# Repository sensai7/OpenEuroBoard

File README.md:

# OpenEuroBoard
Kicad and Gerber files for the manufacturing of electronic synthesizers prototyping and developing, focusing on utilities to prototype Eurorack modules. All the sections in the board are independent from each other (except the Gate/CV generators) that need the 5V regulator part, and can be disregarded if they're not needed for the user application.

(This is from an older version but the features are the same)

## Feature List:
 * Size adjusted to fit exactly a standard sized breadboard.
 * SSD1306 driver based Screen interfaces, with sockets for both 128x64px and 128x32px versions.
 * 2x quad op-amps (TL074) for custom use.
 * 5V regulator and power bus.
 * 4x custom push buttons.
 * MIDI IN/OUT interfaces. MIDI IN is isolated through a optocoupler, MIDI OUT is buffered.
 * 8x custom Minijack sockets.
 * 5x pots, 2x custom pots to connect any desired value. The pots can be easily shorted to ground, +12V, or between their own pins using a jumper.
 * 4x custom SPDT switches.
 * 4x custom LEDs.
 * Small jumper storage.
 * A stereo buffered out with a stereo minijack socket.
 * Custom test points and power bus test points.
 * 2x Gate and CV generators, Both signals being 0~5V.
 * 2x oscillators with low (LFO) and high (Audio rate) range switches and frequency pots.
 * Screw mount holes

## Bill Of Materials:
|Section          |Type             |Model                   |Amount|
|-----------------|-----------------|------------------------|------|
|General          |Male Header      |2x5 dupont header       |2     |
|                 |Female Header    |1x40 dupont header      |2     |
|                 |Voltage regulator|LM1117-5                |1     |
|                 |LED              |3mm Red LED             |1     |
|                 |Resistor         |2.2k                    |1     |
|                 |Capacitor        |100n                    |2     |
|                 |Elec. Capacitor  |10u                     |4     |
|Screen interfaces|Screen           |SSD1306                 |1     |
|quad op-amps     |Op. amp          |TL074                   |2     |
|                 |Capacitor        |100n                    |4     |
|Push buttons     |Push button      |6mm push                |4     |
|MIDI IN-OUT      |Din-5 Connector  |Din-5 Connector         |2     |
|                 |Optocoupler      |6n139                   |1     |
|                 |Dual inverter    |CD40107BE               |1     |
|                 |Diode            |1n4148                  |1     |
|                 |Resistor         |220                     |3     |
|                 |Resistor         |270                     |1     |
|                 |Resistor         |120                     |2     |
|Minijack sockets |Minijack         |Thonkiconn jack         |8     |
|Potentiometer    |Potentiometer    |Alps vertical pot       |5     |
|Switches         |SPDT             |8.5mm SPDT              |4     |
|LEDS             |LED              |3mm Red LED             |4     |
|                 |Resistor         |1k                      |4     |
|Jumper storage   |Jumper           |2.54mm jumper           |5     |
|Stereo out       |Op. amp          |TL072                   |1     |
|                 |Capacitor        |100n                    |2     |
|                 |Minijack         |Vertical stereo jack    |1     |
|Gate generators  |Push button      |6mm push                |2     |
|                 |Resistor         |4.7k                    |2     |
|CV Generators    |Potentiometer    |Alps vertical pot 100k  |2     |
|Oscillators      |Op. amp          |Tl074                   |1     |
|                 |Capacitor        |100n                    |4     |
|                 |Potentiometer    |Alps vertical pot 1M LOG|2     |
|                 |SPDT             |8.5mm SPDT              |2     |
|                 |Capacitor        |1u                      |2     |
|                 |Capacitor        |22n                     |2     |
|                 |Resistor         |1k                      |4     |
|                 |Resistor         |10k                     |4     |
|                 |Resistor         |100k                    |2     |

## Changelog

 * V1.0 First version
 * V1.1 Addressed the issues from [Issue 1](https://github.com/sensai7/OpenEuroBoard/issues/1). Updated Silkscreen

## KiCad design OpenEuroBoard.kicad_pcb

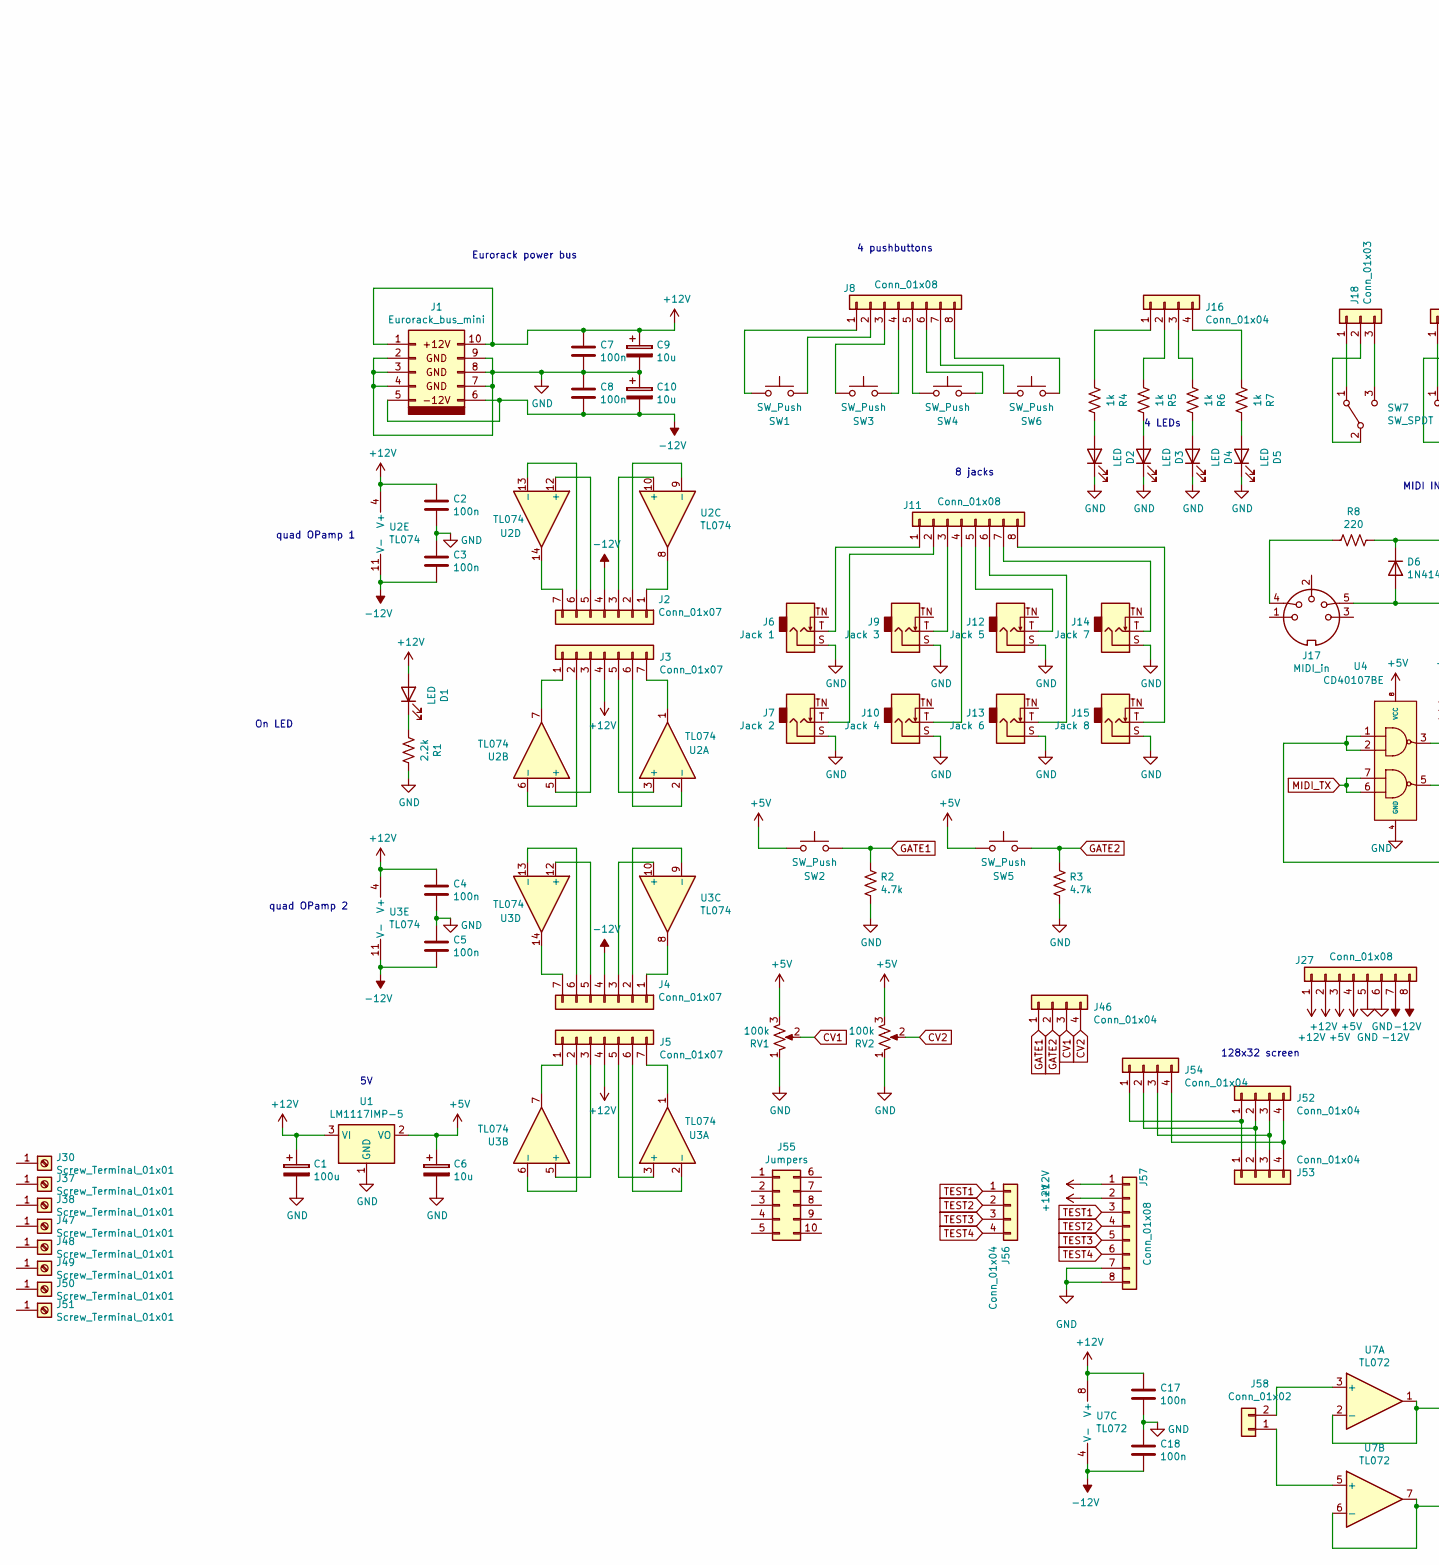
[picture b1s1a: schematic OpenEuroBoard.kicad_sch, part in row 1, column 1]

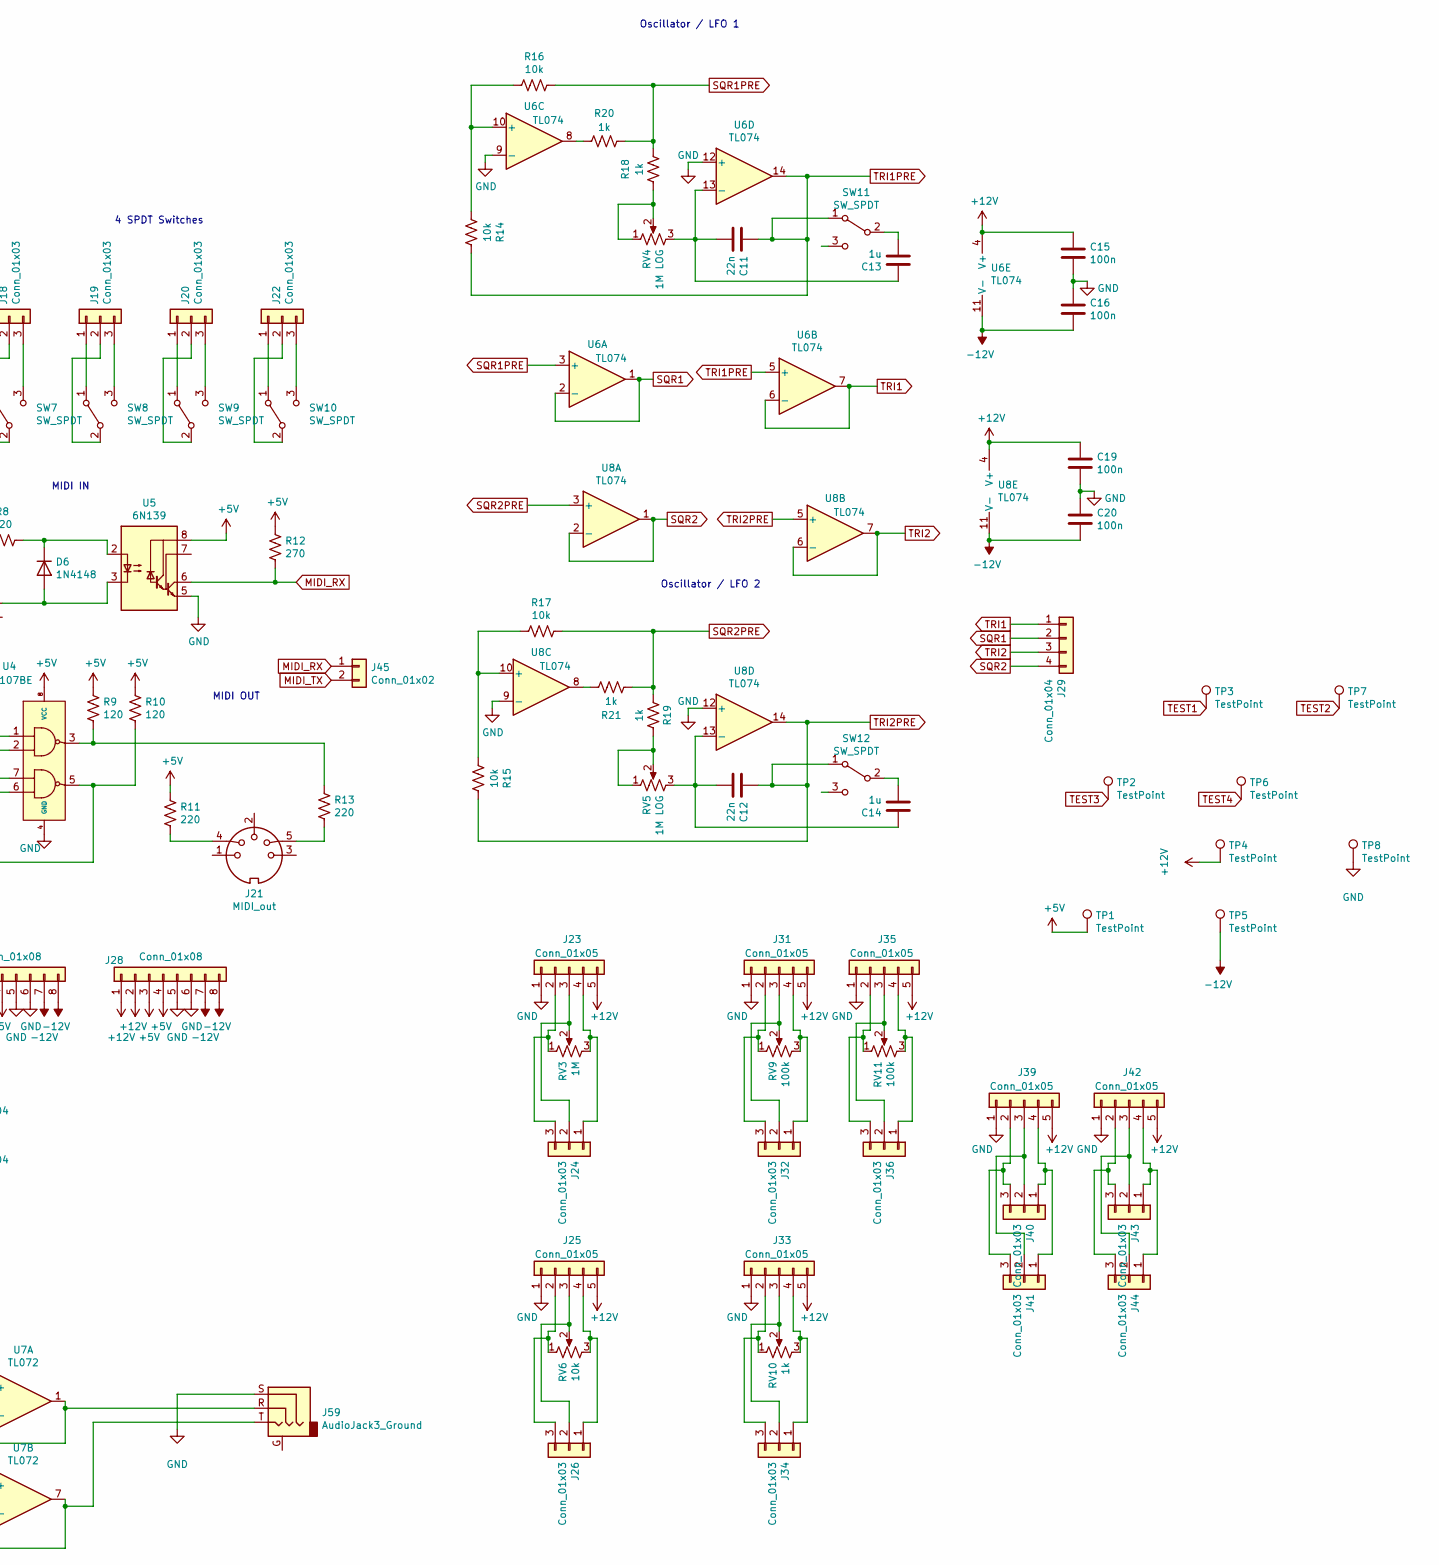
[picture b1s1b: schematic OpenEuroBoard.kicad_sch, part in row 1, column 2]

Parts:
C1: 100u; CP_Radial_D4.0mm_P2.00mm
C2, C3, C4, C5, C7, C8, C15, C16, C17, C18, C19, C20: 100n; C_Disc_D3.4mm_W2.1mm_P2.50mm
C6, C9, C10: 10u; CP_Radial_D4.0mm_P2.00mm
C11, C12: 22n; C_Disc_D3.4mm_W2.1mm_P2.50mm
C13, C14: 1u; C_Disc_D3.4mm_W2.1mm_P2.50mm
D1, D2, D3, D4, D5: LED; LED_D3.0mm_FlatTop
D6: 1N4148; D_DO-35_SOD27_P7.62mm_Horizontal
J1: Eurorack_bus_mini; Eurorack_mini_bus
J2, J3, J4, J5: Conn_01x07; PinHeader_1x07_P2.54mm_Vertical
J6: Jack 1; Jack_3.5mm_QingPu_WQP-PJ398SM_Vertical_CircularHoles
J7: Jack 2; Jack_3.5mm_QingPu_WQP-PJ398SM_Vertical_CircularHoles
J8, J11, J27, J28, J57: Conn_01x08; PinHeader_1x08_P2.54mm_Vertical
J9: Jack 3; Jack_3.5mm_QingPu_WQP-PJ398SM_Vertical_CircularHoles
J10: Jack 4; Jack_3.5mm_QingPu_WQP-PJ398SM_Vertical_CircularHoles
J12: Jack 5; Jack_3.5mm_QingPu_WQP-PJ398SM_Vertical_CircularHoles
J13: Jack 6; Jack_3.5mm_QingPu_WQP-PJ398SM_Vertical_CircularHoles
J14: Jack 7; Jack_3.5mm_QingPu_WQP-PJ398SM_Vertical_CircularHoles
J15: Jack 8; Jack_3.5mm_QingPu_WQP-PJ398SM_Vertical_CircularHoles
J16, J29, J46, J53, J56: Conn_01x04; PinHeader_1x04_P2.54mm_Vertical
J17: MIDI_in; din-5
J18, J19, J20, J22, J24, J26, J32, J34, J36, J40, J41, J43, J44: Conn_01x03; PinHeader_1x03_P2.54mm_Vertical
J21: MIDI_out; din-5
J23, J25, J31, J33, J35, J39, J42: Conn_01x05; PinHeader_1x05_P2.54mm_Vertical
J30, J37, J38, J47, J48, J49, J50, J51: Screw_Terminal_01x01; MountingHole_3.2mm_M3_Pad_Via
J45: Conn_01x02; PinSocket_1x02_P2.54mm_Vertical
J52, J54: Conn_01x04; 0.91 inches 128x32 Screen
J55: Jumpers; PinHeader_2x05_P2.54mm_Vertical
J58: Conn_01x02; PinHeader_1x02_P2.54mm_Vertical
J59: AudioJack3_Ground; Jack Stereo vertical Thonk
R1: 2.2k; R_Axial_DIN0207_L6.3mm_D2.5mm_P7.62mm_Horizontal
R2, R3: 4.7k; R_Axial_DIN0207_L6.3mm_D2.5mm_P7.62mm_Horizontal
R4, R5, R6, R7, R18, R19, R20, R21: 1k; R_Axial_DIN0207_L6.3mm_D2.5mm_P7.62mm_Horizontal
R8, R11, R13: 220; R_Axial_DIN0207_L6.3mm_D2.5mm_P7.62mm_Horizontal
R9, R10: 120; R_Axial_DIN0207_L6.3mm_D2.5mm_P7.62mm_Horizontal
R12: 270; R_Axial_DIN0207_L6.3mm_D2.5mm_P7.62mm_Horizontal
R14, R15, R16, R17: 10k; R_Axial_DIN0207_L6.3mm_D2.5mm_P7.62mm_Horizontal
RV1, RV2, RV9, RV11: 100k; trimmer_alps-rk09k1130ah1
RV3: 1M; trimmer_alps-rk09k1130ah1
RV4, RV5: 1M LOG; trimmer_alps-rk09k1130ah1
RV6: 10k; trimmer_alps-rk09k1130ah1
RV10: 1k; trimmer_alps-rk09k1130ah1
SW1, SW2, SW3, SW4, SW5, SW6: SW_Push; SW_PUSH_6mm_H5mm
SW7, SW8, SW9, SW10, SW11, SW12: SW_SPDT; SPDT_8.5x3.7mm_SS12d00G4
TP1, TP2, TP3, TP4, TP5, TP6, TP7, TP8: TestPoint; TestPoint_THTPad_D3.0mm_Drill1.5mm
U1: LM1117IMP-5; TO-220-3_Horizontal_TabDown
U2, U3: TL074
U4: CD40107BE; DIP-8_W7.62mm_LongPads
U5: 6N139; DIP-8_W7.62mm
U6, U8: TL074; DIP-14_W7.62mm
U7: TL072; DIP-8_W7.62mm_Socket_LongPads

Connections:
+5V: C6.1, J27.3, J27.4, J28.3, J28.4, R9.1, R10.1, R11.1, R12.1, RV1.3, RV2.3, SW2.1, SW5.1, TP1.1, U1.2 (VO), U4.8 (VCC), U5.8 (VCC)
+12V: C1.1, C2.1, C4.1, C7.1, C9.1, C15.1, C17.1, C19.1, D1.2 (A), J1.1, J1.10, J3.4, J5.4, J23.5, J25.5, J27.1, J27.2, J28.1, J28.2, J31.5, J33.5, J35.5, J39.5, J42.5, J57.1, J57.2, TP4.1, U1.3 (VI), U2.4 (V+), U3.4 (V+), U6.4 (V+), U7.8 (V+), U8.4 (V+)
-12V: C3.2, C5.2, C8.2, C10.2, C16.2, C18.2, C20.2, J1.5, J1.6, J2.4, J4.4, J27.7, J27.8, J28.7, J28.8, TP5.1, U2.11 (V-), U3.11 (V-), U6.11 (V-), U7.4 (V-), U8.11 (V-)
CV1: J46.3, RV1.2
CV2: J46.4, RV2.2
GATE1: J46.1, R2.1, SW2.2
GATE2: J46.2, R3.1, SW5.2
GND: C1.2, C2.2, C3.1, C4.2, C5.1, C6.2, C7.2, C8.1, C9.2, C10.1, C15.2, C16.1, C17.2, C18.1, C19.2, C20.1, D2.1 (K), D3.1 (K), D4.1 (K), D5.1 (K), J1.2, J1.3, J1.4, J1.7, J1.8, J1.9, J6.S, J7.S, J9.S, J10.S, J12.S, J13.S, J14.S, J15.S, J23.1, J25.1, J27.5, J27.6, J28.5, J28.6, J31.1, J33.1, J35.1, J39.1, J42.1, J57.7, J57.8, J59.S, R1.1, R2.2, R3.2, RV1.1, RV2.1, TP8.1, U1.1 (GND), U4.4 (GND), U5.5 (GND), U6.9 (-), U6.12 (+), U8.9 (-), U8.12 (+)
MIDI_RX: J45.1, R12.2, U5.6 (VO2)
MIDI_TX: J45.2, U4.6, U4.7
unnamed: D1.1 (K), R1.2
unnamed: D2.2 (A), R4.1
unnamed: D3.2 (A), R5.1
unnamed: D4.2 (A), R6.1
unnamed: D5.2 (A), R7.1
unnamed: D6.2 (A), J17.5, U5.3 (C2)
unnamed: D6.1 (K), R8.1, U5.2 (C1)
unnamed: J2.1, U2.8
unnamed: J2.2, U2.9 (-)
unnamed: J2.3, U2.10 (+)
unnamed: J2.5, U2.12 (+)
unnamed: J2.6, U2.13 (-)
unnamed: J2.7, U2.14
unnamed: J3.1, U2.7
unnamed: J3.2, U2.6 (-)
unnamed: J3.3, U2.5 (+)
unnamed: J3.5, U2.3 (+)
unnamed: J3.6, U2.2 (-)
unnamed: J3.7, U2.1
unnamed: J4.1, U3.8
unnamed: J4.2, U3.9 (-)
unnamed: J4.3, U3.10 (+)
unnamed: J4.5, U3.12 (+)
unnamed: J4.6, U3.13 (-)
unnamed: J4.7, U3.14
unnamed: J5.1, U3.7
unnamed: J5.2, U3.6 (-)
unnamed: J5.3, U3.5 (+)
unnamed: J5.5, U3.3 (+)
unnamed: J5.6, U3.2 (-)
unnamed: J5.7, U3.1
unnamed: J8.1, SW1.1
unnamed: J8.2, SW1.2
unnamed: J8.3, SW3.1
unnamed: J8.4, SW3.2
unnamed: J8.5, SW4.1
unnamed: J8.6, SW4.2
unnamed: J8.7, SW6.1
unnamed: J8.8, SW6.2
unnamed: J6.T, J11.1
unnamed: J7.T, J11.2
unnamed: J9.T, J11.3
unnamed: J10.T, J11.4
unnamed: J11.5, J12.T
unnamed: J11.6, J13.T
unnamed: J11.7, J14.T
unnamed: J11.8, J15.T
unnamed: J16.1, R4.2
unnamed: J16.2, R5.2
unnamed: J16.3, R6.2
unnamed: J16.4, R7.2
unnamed: J17.4, R8.2
unnamed: J18.1, SW7.1 (A)
unnamed: J18.2, SW7.2 (B)
unnamed: J18.3, SW7.3 (C)
unnamed: J19.1, SW8.1 (A)
unnamed: J19.2, SW8.2 (B)
unnamed: J19.3, SW8.3 (C)
unnamed: J20.1, SW9.1 (A)
unnamed: J20.2, SW9.2 (B)
unnamed: J20.3, SW9.3 (C)
unnamed: J21.4, R11.2
unnamed: J21.5, R13.2
unnamed: J22.1, SW10.1 (A)
unnamed: J22.2, SW10.2 (B)
unnamed: J22.3, SW10.3 (C)
unnamed: J23.2, J24.3, RV3.1
unnamed: J23.3, J24.2, RV3.2
unnamed: J23.4, J24.1, RV3.3
unnamed: J25.2, J26.3, RV6.1
unnamed: J25.3, J26.2, RV6.2
unnamed: J25.4, J26.1, RV6.3
unnamed: J31.2, J32.3, RV9.1
unnamed: J31.3, J32.2, RV9.2
unnamed: J31.4, J32.1, RV9.3
unnamed: J33.2, J34.3, RV10.1
unnamed: J33.3, J34.2, RV10.2
unnamed: J33.4, J34.1, RV10.3
unnamed: J35.2, J36.3, RV11.1
unnamed: J35.3, J36.2, RV11.2
unnamed: J35.4, J36.1, RV11.3
unnamed: J39.2, J40.3, J41.3
unnamed: J39.3, J40.2, J41.2
unnamed: J39.4, J40.1, J41.1
unnamed: J42.2, J43.3, J44.3
unnamed: J42.3, J43.2, J44.2
unnamed: J42.4, J43.1, J44.1
unnamed: J52.1, J53.1, J54.1
unnamed: J52.2, J53.2, J54.2
unnamed: J52.3, J53.3, J54.3
unnamed: J52.4, J53.4, J54.4
unnamed: J58.1, U7.5 (+)
unnamed: J58.2, U7.3 (+)
unnamed: R10.2, U4.1, U4.2, U4.5
unnamed: R9.2, R13.1, U4.3
unnamed: R18.1, RV4.1, RV4.2
unnamed: R19.1, RV5.1, RV5.2
unnamed: R20.1, U6.8
unnamed: R21.2, U8.8
unnamed: C13.2, SW11.2 (B)
unnamed: C14.2, SW12.2 (B)
unnamed: R14.2, R16.2, U6.10 (+)
unnamed: C11.2, C13.1, RV4.3, U6.13 (-)
unnamed: J59.R, U7.1, U7.2 (-)
unnamed: J59.T, U7.6 (-), U7.7
unnamed: R15.2, R17.2, U8.10 (+)
unnamed: C12.2, C14.1, RV5.3, U8.13 (-)
SQR1: J29.2, U6.1, U6.2 (-)
SQR1PRE: R16.1, R18.2, R20.2, U6.3 (+)
SQR2: J29.4, U8.1, U8.2 (-)
SQR2PRE: R17.1, R19.2, R21.1, U8.3 (+)
TEST1: J56.1, J57.3, TP3.1
TEST2: J56.2, J57.4, TP7.1
TEST3: J56.3, J57.5, TP2.1
TEST4: J56.4, J57.6, TP6.1
TRI1: J29.1, U6.6 (-), U6.7
TRI1PRE: C11.1, R14.1, SW11.1 (A), U6.5 (+), U6.14
TRI2: J29.3, U8.6 (-), U8.7
TRI2PRE: C12.1, R15.1, SW12.1 (A), U8.5 (+), U8.14

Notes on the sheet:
4 pushbuttons
MIDI OUT
8 jacks
quad OPamp 1
4 SPDT Switches
128x32 screen
Eurorack power bus
quad OPamp 2
Oscillator / LFO 2
MIDI IN
4 LEDs
Oscillator / LFO 1
On LED

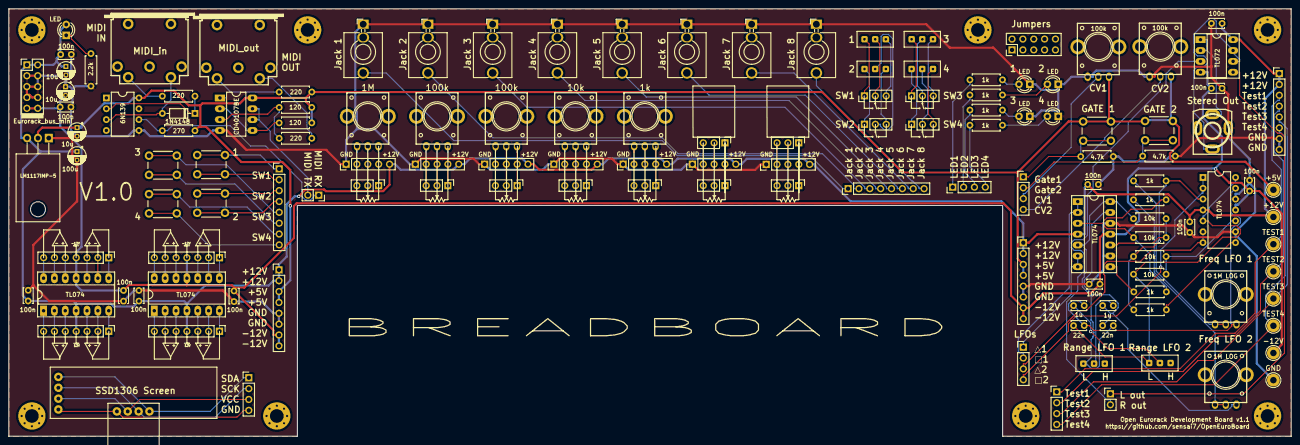
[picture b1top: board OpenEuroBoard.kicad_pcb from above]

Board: 2 copper layers, 300.0 x 100.0 mm, 143 parts (0 on the bottom side), 129 nets.

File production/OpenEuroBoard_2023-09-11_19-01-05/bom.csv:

Designator,Footprint,Quantity,Value,LCSC Part #
C1,CP_Radial_D4.0mm_P2.00mm,1,100u,
"C10, C6, C9",CP_Radial_D4.0mm_P2.00mm,3,10u,
"C11, C12",C_Disc_D3.4mm_W2.1mm_P2.50mm,2,22n,
"C13, C14",C_Disc_D3.4mm_W2.1mm_P2.50mm,2,1u,
"C15, C16, C17, C18, C19, C2, C20, C3, C4, C5, C7, C8",C_Disc_D3.4mm_W2.1mm_P2.50mm,12,100n,
"D1, D2, D3, D4, D5",LED_D3.0mm_FlatTop,5,LED,
D6,D_DO-35_SOD27_P7.62mm_Horizontal,1,1N4148,
J1,Eurorack_mini_bus,1,Eurorack_bus_mini,
J10,Jack_3.5mm_QingPu_WQP-PJ398SM_Vertical_CircularHoles,1,Jack 4,
"J11, J27, J28, J57, J8",PinHeader_1x08_P2.54mm_Vertical,5,Conn_01x08,
J12,Jack_3.5mm_QingPu_WQP-PJ398SM_Vertical_CircularHoles,1,Jack 5,
J13,Jack_3.5mm_QingPu_WQP-PJ398SM_Vertical_CircularHoles,1,Jack 6,
J14,Jack_3.5mm_QingPu_WQP-PJ398SM_Vertical_CircularHoles,1,Jack 7,
J15,Jack_3.5mm_QingPu_WQP-PJ398SM_Vertical_CircularHoles,1,Jack 8,
"J16, J29, J46, J53, J56",PinHeader_1x04_P2.54mm_Vertical,5,Conn_01x04,
J17,din-5,1,MIDI_in,
"J18, J19, J20, J22, J24, J26, J32, J34, J36, J40, J41, J43, J44",PinHeader_1x03_P2.54mm_Vertical,13,Conn_01x03,
"J2, J3, J4, J5",PinHeader_1x07_P2.54mm_Vertical,4,Conn_01x07,
J21,din-5,1,MIDI_out,
"J23, J25, J31, J33, J35, J39, J42",PinHeader_1x05_P2.54mm_Vertical,7,Conn_01x05,
"J30, J37, J38, J47, J48, J49, J50, J51",MountingHole_3.2mm_M3_Pad_Via,8,Screw_Terminal_01x01,
J45,PinSocket_1x02_P2.54mm_Vertical,1,Conn_01x02,
"J52, J54",0.91 inches 128x32 Screen,2,Conn_01x04,
J55,PinHeader_2x05_P2.54mm_Vertical,1,Jumpers,
J58,PinHeader_1x02_P2.54mm_Vertical,1,Conn_01x02,
J59,Jack Stereo vertical Thonk,1,AudioJack3_Ground,
J6,Jack_3.5mm_QingPu_WQP-PJ398SM_Vertical_CircularHoles,1,Jack 1,
J7,Jack_3.5mm_QingPu_WQP-PJ398SM_Vertical_CircularHoles,1,Jack 2,
J9,Jack_3.5mm_QingPu_WQP-PJ398SM_Vertical_CircularHoles,1,Jack 3,
R1,R_Axial_DIN0207_L6.3mm_D2.5mm_P7.62mm_Horizontal,1,2.2k,
"R10, R9",R_Axial_DIN0207_L6.3mm_D2.5mm_P7.62mm_Horizontal,2,120,
"R11, R13, R8",R_Axial_DIN0207_L6.3mm_D2.5mm_P7.62mm_Horizontal,3,220,
R12,R_Axial_DIN0207_L6.3mm_D2.5mm_P7.62mm_Horizontal,1,270,
"R14, R15, R16, R17",R_Axial_DIN0207_L6.3mm_D2.5mm_P7.62mm_Horizontal,4,10k,
"R18, R19, R20, R21, R4, R5, R6, R7",R_Axial_DIN0207_L6.3mm_D2.5mm_P7.62mm_Horizontal,8,1k,
"R2, R3",R_Axial_DIN0207_L6.3mm_D2.5mm_P7.62mm_Horizontal,2,4.7k,
"RV1, RV11, RV2, RV9",trimmer_alps-rk09k1130ah1,4,100k,
RV10,trimmer_alps-rk09k1130ah1,1,1k,
RV3,trimmer_alps-rk09k1130ah1,1,1M,
"RV4, RV5",trimmer_alps-rk09k1130ah1,2,1M LOG,
RV6,trimmer_alps-rk09k1130ah1,1,10k,
"SW1, SW2, SW3, SW4, SW5, SW6",SW_PUSH_6mm_H5mm,6,SW_Push,
"SW10, SW11, SW12, SW7, SW8, SW9",SPDT_8.5x3.7mm_SS12d00G4,6,SW_SPDT,
"TP1, TP2, TP3, TP4, TP5, TP6, TP7, TP8",TestPoint_THTPad_D3.0mm_Drill1.5mm,8,TestPoint,
U1,TO-220-3_Horizontal_TabDown,1,LM1117IMP-5,
"U2, U3, U6",DIP-14_W7.62mm_Socket_LongPads,3,TL074,
U4,DIP-8_W7.62mm_LongPads,1,CD40107BE,
U5,DIP-8_W7.62mm,1,6N139,
U7,DIP-8_W7.62mm_Socket_LongPads,1,TL072,
U8,DIP-14_W7.62mm,1,TL074,

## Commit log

2020-08-06 Initial commit for real
2020-08-16 Silkscreen and general rework
2020-08-30 Finished layout, silkscreen and routing
    also fixed minijack footprint
2020-08-30 finished silkscreen, fixed some minor errors
2020-12-20 stuff
2021-01-10 Added BOM
2021-01-10 Added Gerber files
2021-01-10 Small change
2023-09-11 Version 1.1
2023-09-11 Update README.md formatting
